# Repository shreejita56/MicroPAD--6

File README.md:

# MicroPAD--6

So I made a 6 Switch MacroPad ,which has a rotor encoder at the top for brightness controlee as well . It is based on Xiao Rp2040 and has per switch LED as well and the display shows how much time are you working for . Also we used diodes to prevent ghosting .The PCB was designed on kicad and CAD was done on Fusion . firmware was written in VS-Code. It has a very compact design.

## Features
 - Based on Xiao Rp2040 
 - had compact layout
 - Per Switch LED and diode for ghosting prevention
 - USB-C Type for Connection
 - Uplifted CAD Design for comfortable typing

## BOM 

|Name|Quantity|Total Price (USD)|Link|
|-|-|-|-|
| PCB (JLCPCB) | -- | 4.00 |https://jlcpcb.com|
| PCB Shipping |-- | 12.74 |https://jlcpcb.com|
| Seeed Studio XIAO RP2040 | 1 | 16.10 |https://amzn.in/d/03AnHkRA|
| Switches + Keycaps | 6 |0.0 **Alread Have**|https://meckeys.com/shop/accessories/keyboard-accessories/key-switches/akko-v3-pro-cream-black-switch/|
| Diodes | 6 | 0.00 **Alread Have**|https://www.amazon.in/Electronic-Spices-Inverse-Voltage-Rectifier/dp/B0BGX995MB|
| 0.91" OLED Screen | 1 | 0.00 **Alread Have** |https://www.amazon.in/Robocraze-Display-Module-Interface-Arduino/dp/B084H9HLCS|
| Rotary Encoder | 1 | 0.00 **Alread Have** |(https://www.amazon.in/CentIoT-Encoder-Digital-Potentiometer-Control/dp/B0888RVZSN|
| SK6812MINI-E | 6 | 0.00 **Alread Have** | https://www.etstore.in/products/e9974) |
|HOTSWAP| 1 PACK (10 pieces )|0.0 |https://meckeys.com/shop/accessories/keyboard-accessories/key-switches/kailh-hot-swap-socket/

## Total Cost

**Total price 32.74**

### Schematic<br><br>

###  PCB Design<br><br>

### 3D Render <br><br>

## Assembly Instructions

So first we will solder the Xiao Rp2040 Board on the lower side of the PCB. We will be using SMD Soldering for that . Same for the Hot Swap as well . For the Hot Swap connection . first tin the pads well with solder then place the hot swap and use the soldering iron to heat it. the hot swaps will automatically align perfectly then add the diodes and solder them . for the LEDS first place the leds onto the pad then solder it via using a decent amount of flux. SO that the connections are prefect then at the END align the screen and solder it though the pins . then place it on the base then add the switches onto the hotswap and place the top layer CAD . Screw everything down and you are good to go.

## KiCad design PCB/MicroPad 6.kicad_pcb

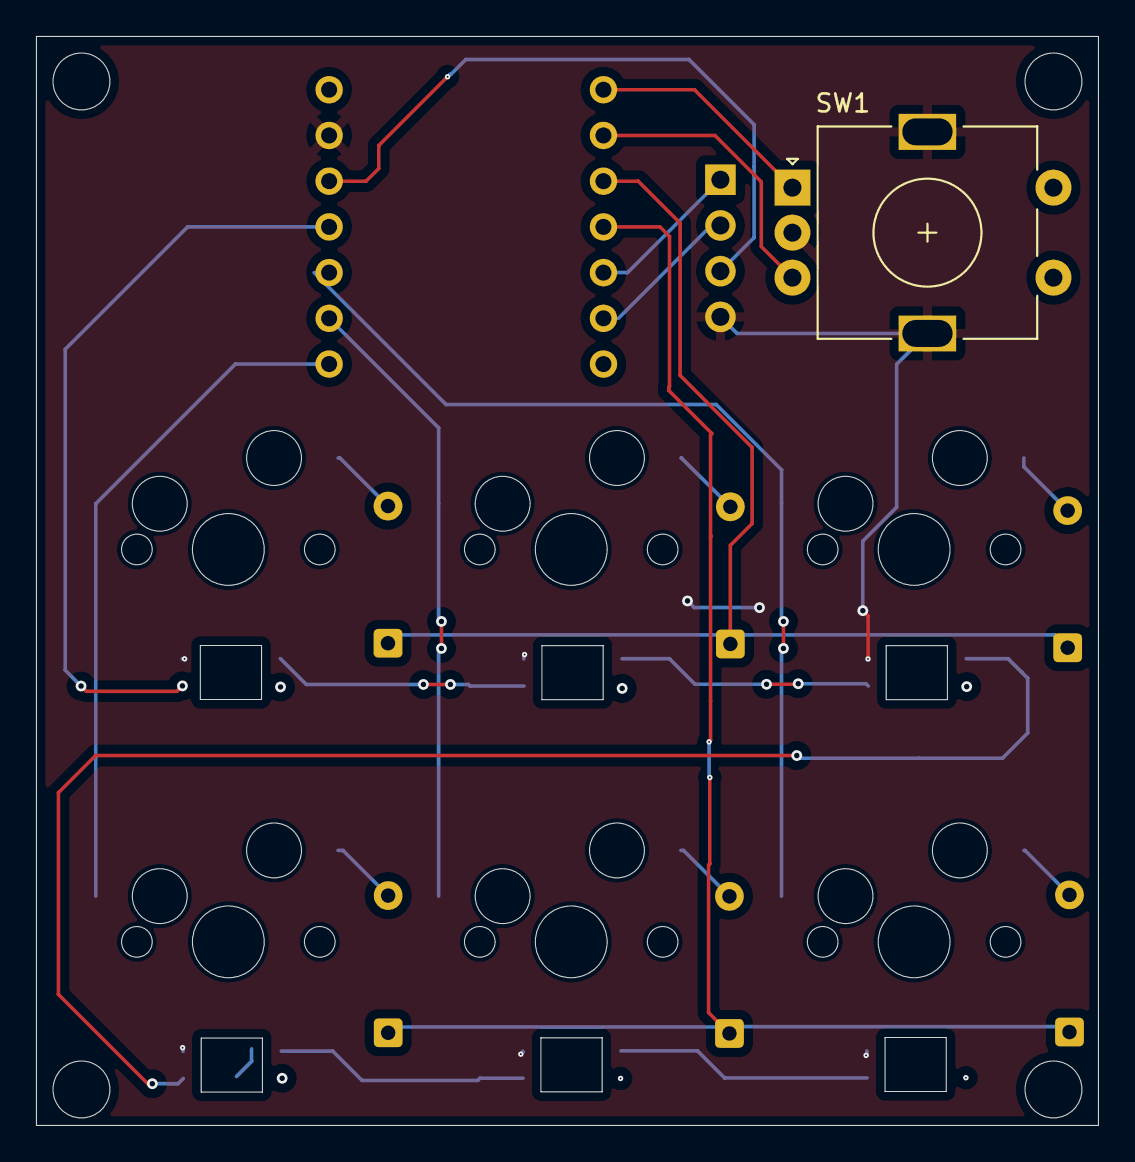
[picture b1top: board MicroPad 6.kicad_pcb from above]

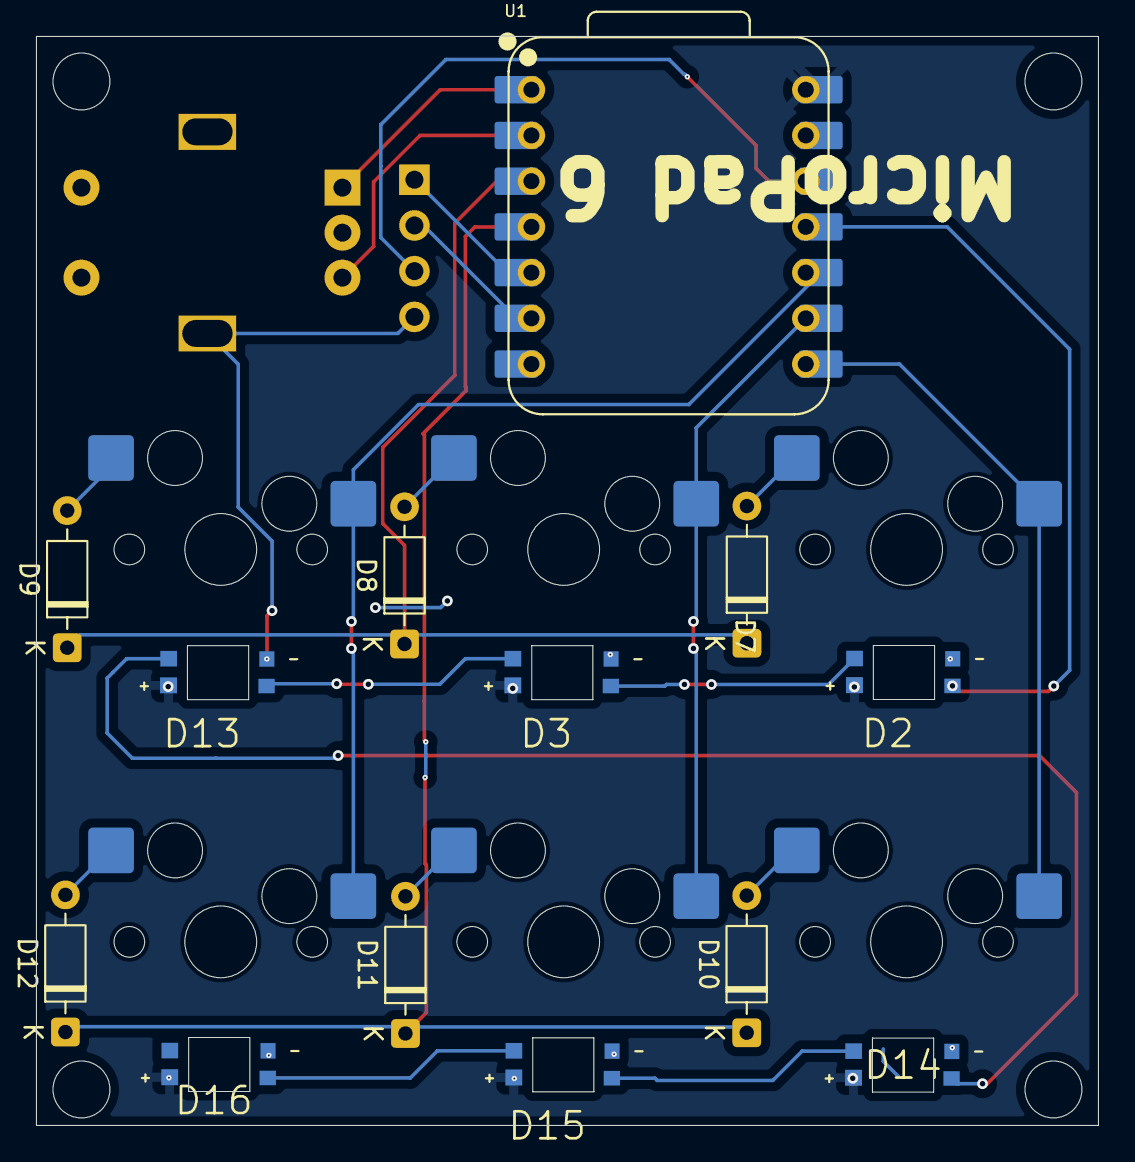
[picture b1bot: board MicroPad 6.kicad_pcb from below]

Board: 2 copper layers, 59.0 x 60.5 mm, 21 parts (19 on the bottom side), 24 nets.

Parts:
D2, D3, D13, D14, D15, D16: SK6812-E; LED_SK6812-E
D7, D8, D9, D10, D11, D12: 1N4148; D_DO-35_SOD27_P7.62mm_Horizontal
J2: Conn_01x04_Pin; OLED_128x32
SW1: RotaryEncoder_Switch_MP; RotaryEncoder_Alps_EC11E-Switch_Vertical_H20mm
SW7, SW8, SW9, SW13, SW14, SW15: SW_Push; MX100H
U1: XIAO-RP2040-DIP

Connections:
3.3V: J2.3, U1.12 (3V3)
5V: D2.1 (VDD), D3.1 (VDD), D13.1 (VDD), D14.1 (VDD), D15.1 (VDD), D16.1 (VDD), U1.14 (VBUS)
A1: SW1.A, U1.1 (GPIO26/ADC0/A0)
B1: SW1.B, U1.2 (GPIO27/ADC1/A1)
C1: SW7.2, SW13.2, U1.8 (GPIO1/RX)
C2: SW8.2, SW14.2, U1.9 (GPIO2/SCK)
C3: SW9.2, SW15.2, U1.10 (GPIO4/MISO)
GND: D2.3 (GND), D3.3 (GND), D13.3 (GND), D14.3 (GND), D15.3 (GND), D16.3 (GND), J2.4, SW1.C, SW1.MP, U1.13 (GND)
LED: D2.4 (DIN), U1.11 (GPIO3/MOSI)
unnamed: D2.2 (DOUT), D3.4 (DIN)
unnamed: D7.2 (A), SW7.1
unnamed: D8.2 (A), SW8.1
unnamed: D9.2 (A), SW9.1
unnamed: D10.2 (A), SW13.1
unnamed: D11.2 (A), SW14.1
unnamed: D12.2 (A), SW15.1
unnamed: D3.2 (DOUT), D13.4 (DIN)
unnamed: D13.2 (DOUT), D14.4 (DIN)
unnamed: D14.2 (DOUT), D15.4 (DIN)
unnamed: D15.2 (DOUT), D16.4 (DIN)
R1: D7.1 (K), D8.1 (K), D9.1 (K), U1.3 (GPIO28/ADC2/A2)
R2: D10.1 (K), D11.1 (K), D12.1 (K), U1.4 (GPIO29/ADC3/A3)
SCl: J2.2, U1.6 (GPIO7/SCL)
SDA: J2.1, U1.5 (GPIO6/SDA)
